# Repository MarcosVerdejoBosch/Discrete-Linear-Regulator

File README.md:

# Discrete Linear Regulator

## Download the 36 validated simulations

**[Download the assembled LTspice ZIP](https://github.com/MarcosVerdejoBosch/Discrete-Linear-Regulator/releases/download/simulations-package-v1.0.1/Discrete-Linear-Regulator-36-LTspice-v1.0.1.zip)** — 16 principal cases + 20 SIM-09 variants, with model libraries, symbols, saved plots and bias files. Extract the entire ZIP, open an ASC in `Simulaciones`, select the reference solver shown in `README.md`, and press **Run**. No CMD or Python is required. [Contents, dependencies and verification scope](publication/PORTABLE_PACKAGE.md).

**Simulation baseline closed — 2026-10-07.** The builder validated the 16 principal entries and all 20 additional SIM-09 cases. The exact local ASC/PLT files are preserved, including the final annotation layout. [Closure and recovery scope](publication/SIMULATIONS_V1.md). Open the prepared `.asc` in LTspice and press **Run**; launchers are optional. External models remain necessary. Hardware characterization and the later editorial review of the report remain separate.

A largely discrete linear regulator with selectable **5 V / 3.3 V outputs**, a fabricated PCB, and documented LTspice studies.

**Review snapshot â€” September 2026.** The assembled board has produced both output voltages. Detailed bench characterization remains pending. Numerical results below are simulations, not hardware specifications.

## Download the frozen KiCad design

**[Download the hardware-v1.0 package](https://github.com/MarcosVerdejoBosch/Discrete-Linear-Regulator/releases/download/hardware-v1.0/Discrete-Linear-Regulator-KiCad-v1.0.zip)** — final schematic, PCB, project, schematic PDF and the unchanged `Manufacturing_Regulador.zip` sent to JLCPCB. Extract and open the project in KiCad 9. [Scope and traceability](hardware/README.md).

The installed BOM still needs confirmation. [Physical measurement banks and available equipment](measurements/README.md) are documented separately; quantitative characterization remains pending.

## Run in LTspice

**2026-09-24 revalidation:** all 16 primary SIM-01–SIM-09 scenarios completed locally with LTspice 17.1.15. U17 now uses the official IRF4905 model in the full-circuit cases; report figures and tables were regenerated. The SIM-09 fixed-bias core is unchanged and was rerun. [Scope, numerical settings and evidence](publication/U17_REVALIDATION_2026-09-24.md).

Use the assembled release ZIP linked above for direct ASC execution. The older `PREPARAR_LTSPICE.cmd` and launchers are retained as optional source-development tools; they are not part of the downloadable simulation package.

The assembled package includes the supplied external dependencies. A plain **Code → Download ZIP** source snapshot is different from that package. Windows and an installed LTspice are required; see the release instructions for solver selection and third-party notices.

## Start here

- **[Read the report (PDF)](docs/regulator.pdf)** â€” architecture, implementation, simulation results and limitations.
- [Simulation index](simulation/README.md) â€” SIM-01 through SIM-09.
- [What is verified and what remains](publication/REVIEW_STATUS.md).
- [Current organized KiCad project](hardware/kicad/Regulador.kicad_pro), [schematic](hardware/kicad/Regulador.kicad_sch), [PCB](hardware/kicad/Regulador.kicad_pcb).
- [PCB routing atlas](docs/figures/pcb_subcircuit_atlas.pdf) - four component-level maps: power path, current sensing/limiting, enable control and startup. [Sources and regeneration](hardware/PCB_DOCUMENTATION.md).
- [3D board views](docs/figures/pcb_3d_views.pdf) - KiCad rendering of the final layout; standard package models and socket representations.
- [Original published KiCad snapshot](hardware/legacy-github/) â€” retained separately; it differs from the organized copy.

## Current stability finding

The nominal bench uses a 1 uF output capacitor and an **external 1 ohm series resistor**. Intrinsic capacitor ESR is additional and remains uncharacterized. The installed capacitor was identified by the builder as radial tantalum, sold as 1 uF / 35 V.

The fixed-bias regulation-core studies do **not** establish capacitor-free operation across the load range: without the external output capacitor, the near-no-load cases have negative loop margins and persistent oscillation in the corresponding transient checks. Increasing capacitance to 10 uF improves phase margin at approximately 1 A but reduces it near no load. This is not a universal recommendation for an unspecified electrolytic capacitor.

[Output-capacitor comparison and conditions](simulation/tests/SIM-09_loop_stability/results/output_cap_options/README.md).

## Repository structure

| Folder | Contents |
|---|---|
| `docs/` | Compiled report, LaTeX source, bibliography and report figures |
| `hardware/kicad/` | Organized board project |
| `hardware/legacy-github/` | Previously published board files, preserved for comparison |
| `simulation/ltspice/` | Selected scenario definitions and saved bias files |
| `simulation/tests/` | Methods, extracted metrics, selected CSVs, scripts and diagnostic comparisons |
| `publication/` | Snapshot status and provenance manifest |

## Reproduction status

The PDF is ready to read. LaTeX build instructions are in [docs/README.md](docs/README.md).

**The self-contained 36-case LTspice package is available through the release link above.** It includes the supplied models and symbols; see [package contents and verification](publication/PORTABLE_PACKAGE.md). The older [local preparation workflow](simulation/LOCAL_REVIEW.md) is retained for source-development history. Large RAW files and duplicate simulator logs remain in the local evidence archive. SHA256 records refer to those original files. Some analysis scripts require the RAW archive; preparation scripts may require additional original baseline files. Selected CSV exports support inspection without LTspice.

Scenario copies use relative model filenames. A fresh prepared folder was checked against the accepted sources, all 16 primary netlists were generated, and both SIM-09 modes were exercised through the launchers. This is local reproduction evidence, not cross-machine qualification. The [original manifest](publication/manifest.json) is historical; the [current revalidation record](publication/U17_REVALIDATION_2026-09-24.md) identifies the new results. Hardware measurements remain pending.

## License

The repository's existing [MIT license](LICENSE) is retained for project-owned material. Third-party component models and cited publications retain their own terms and are not relicensed by this repository.

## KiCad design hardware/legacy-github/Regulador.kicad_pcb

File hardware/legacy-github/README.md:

Previously published KiCad snapshot, preserved from commit 7b13f20.
The organized working copy is in ../kicad. The files differ; no equivalence is claimed.

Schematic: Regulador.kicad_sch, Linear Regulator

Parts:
C1, C2, C9, C14, C16: 100n; C_Rect_L7.2mm_W3.0mm_P5.00mm_FKS2_FKP2_MKS2_MKP2
C3: 33n; C_Rect_L7.0mm_W2.5mm_P5.00mm
C4, C5: 100p; C_Disc_D3.8mm_W2.6mm_P2.50mm
C6: 3.9n; C_Rect_L7.0mm_W2.0mm_P4.00mm
C7: 4.7n; C_Rect_L7.0mm_W2.0mm_P4.00mm
C8, C11, C13: 1u; CP_Radial_Tantal_D4.5mm_P2.50mm
C10: 6.8u; CP_Radial_Tantal_D5.0mm_P2.50mm
C12, C20, C21: 10u; CP_Radial_D5.0mm_P2.50mm
C15: 330n; C_Rect_L7.2mm_W4.5mm_P5.00mm_FKS2_FKP2_MKS2_MKP2
C17, C22: 22n; C_Rect_L7.2mm_W3.0mm_P5.00mm_FKS2_FKP2_MKS2_MKP2
C18, C19: 10n; C_Rect_L7.0mm_W2.5mm_P5.00mm
D1, D2, D3, D8, D9, D10, D13, D14, D15, D19: D_Zener; D_DO-35_SOD27_P7.62mm_Horizontal
D4, D5, D6, D7, D11, D12, D17, D18: 1N5819; D_DO-41_SOD81_P10.16mm_Horizontal
D16: LED; LED_D5.0mm
D20: TYN612; TO-220-3_Vertical
D21: 1N4148; D_DO-35_SOD27_P7.62mm_Horizontal
F1: Fuse; Fuseholder_Clip-5x20mm_Littelfuse_445-030_Inline_P20.50x5.2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
H1, H2, H3, H4: MountingHole_Pad; MountingHole_4.3mm_M4_Pad_TopOnly
INPUT1: Conn_01x02_Pin; TerminalBlock_P5.08mm
OUTPUT1: Conn_01x02_Pin; TerminalBlock_P5.08mm
Q1, Q2, Q10, Q11, Q14, Q16, Q17: BC557; TO92-Custom
Q3: BC807; SOT-23
Q4: IRF7328; SOIC-8_3.9x4.9mm_P1.27mm
Q6, Q12, Q18, Q20: IRFZ44N; TO-220-3_Vertical
Q7, Q13, Q19: 2N7000; TO92-Custom
Q8, Q21: J175; TO-92_Inline_Wide
Q15, Q23, Q24, Q25, Q26, Q27: BC547; TO92-Custom
Q_PASS1: TIP42C; TO-220-3_Vertical
Q_POL1: IRF4905; TO-220-3_Vertical
R1, R2: 200; R_Axial_DIN0207_L6.3mm_D2.5mm_P7.62mm_Horizontal
R3, R4: 270; R_Axial_DIN0207_L6.3mm_D2.5mm_P7.62mm_Horizontal
R5, R6, R9, R10, R29, R32, R48, R49, R52, R60, R61: 5.6k; R_Axial_DIN0207_L6.3mm_D2.5mm_P7.62mm_Horizontal
R12, R13, R14, R15, R16, R20, R28, R51, R54, R80, R83, R86, R89: 100; R_Axial_DIN0207_L6.3mm_D2.5mm_P7.62mm_Horizontal
R17, R21: 10; R_Axial_DIN0207_L6.3mm_D2.5mm_P7.62mm_Horizontal
R18, R19, R27, R50, R62: 20k; R_Axial_DIN0207_L6.3mm_D2.5mm_P7.62mm_Horizontal
R22, R44, R78: 7.5k; R_Axial_DIN0207_L6.3mm_D2.5mm_P7.62mm_Horizontal
R24, R63: 15k; R_Axial_DIN0207_L6.3mm_D2.5mm_P7.62mm_Horizontal
R30, R31, R70, R73, R79: 3.3k; R_Axial_DIN0207_L6.3mm_D2.5mm_P7.62mm_Horizontal
R33, R34: 1k; R_Axial_DIN0207_L6.3mm_D2.5mm_P7.62mm_Horizontal
R35, R36, R39, R40, R56, R57, R58, R65, R69, R95, R96, R103: 10k; R_Axial_DIN0207_L6.3mm_D2.5mm_P7.62mm_Horizontal
R37, R105, R107: 2k; R_Axial_DIN0207_L6.3mm_D2.5mm_P7.62mm_Horizontal
R38: 1,6k; R_Axial_DIN0207_L6.3mm_D2.5mm_P7.62mm_Horizontal
R42: 510; R_Axial_DIN0207_L6.3mm_D2.5mm_P7.62mm_Horizontal
R43, R53: 1; R_Axial_DIN0207_L6.3mm_D2.5mm_P7.62mm_Horizontal
R55, R88: 4.7k; R_Axial_DIN0207_L6.3mm_D2.5mm_P7.62mm_Horizontal
R66, R74, R77, R87, R92, R94, R97, R99, R104, R108: 100k; R_Axial_DIN0207_L6.3mm_D2.5mm_P7.62mm_Horizontal
R67, R68: 51k; R_Axial_DIN0207_L6.3mm_D2.5mm_P7.62mm_Horizontal
R71, R72: 10Meg; R_Axial_DIN0204_L3.6mm_D1.6mm_P5.08mm_Horizontal
R81: 68k; R_Axial_DIN0207_L6.3mm_D2.5mm_P7.62mm_Horizontal
R82: 680; R_Axial_DIN0207_L6.3mm_D2.5mm_P7.62mm_Horizontal
R90, R91, R93: 47k; R_Axial_DIN0207_L6.3mm_D2.5mm_P7.62mm_Horizontal
R98: 1.6k; R_Axial_DIN0207_L6.3mm_D2.5mm_P7.62mm_Horizontal
R100: 330; R_Axial_DIN0207_L6.3mm_D2.5mm_P7.62mm_Horizontal
R102, R109: 1Meg; R_Axial_DIN0207_L6.3mm_D2.5mm_P7.62mm_Horizontal
R106: 470; R_Axial_DIN0207_L6.3mm_D2.5mm_P7.62mm_Horizontal
RV1, RV2, RV3, RV4, RV5, RV6, RV7, RV8, RV9, RV10, RV11, RV12, RV13: R_Potentiometer; Potentiometer_Bourns_3296W_Vertical
Rsns1: 0.1; R_Axial_DIN0516_L15.5mm_D5.0mm_P20.32mm_Horizontal
SW1: SW_SPDT; SWITCH1; Manufacturer_Part_Number MFP113D-RA
TP4, TP5, TP6, TP7, TP8, TP9, TP10, TP11, TP16, TP17, TP18, TP19, TP20, TP21, TP22, TP23, TP26, TP27, TP28, TP29, TP30: TestPoint; TestPoint_THTPad_2.0x2.0mm_Drill1.0mm
TP24, TP25: TestPoint; TestPoint_THTPad_1.0x1.0mm_Drill0.5mm
TP_3.3V1: TestPoint; TestPoint_THTPad_2.0x2.0mm_Drill1.0mm
TP_FB1: TestPoint; TestPoint_THTPad_2.0x2.0mm_Drill1.0mm
TP_GND_IN1: TestPoint; TestPoint_THTPad_D4.0mm_Drill2.0mm
TP_GND_OUT1: TestPoint; TestPoint_THTPad_D4.0mm_Drill2.0mm
TP_Isns1: TestPoint; TestPoint_THTPad_2.0x2.0mm_Drill1.0mm
TP_OUT1: TestPoint; TestPoint_THTPad_D4.0mm_Drill2.0mm
TP_SW1: TestPoint; TestPoint_THTPad_2.0x2.0mm_Drill1.0mm
TP_TTL1: TestPoint; TestPoint_THTPad_2.0x2.0mm_Drill1.0mm
TP_VCC1: TestPoint; TestPoint_THTPad_D4.0mm_Drill2.0mm
TP_VREF1: TestPoint; TestPoint_THTPad_2.0x2.0mm_Drill1.0mm
U1, U2, U3: CA3096; DIP-16
U4: LM324A; CERDIP-14
U5, U6, U8, U11: TL431LP; TO92-Custom
U7: LM339; CERDIP-14
U9: LM393; CERDIP-8
U10: ICL7660; DIP-8_W7.62mm_Socket

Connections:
1: R79.1, R82.2, R90.1, TP23.1, U7.13
2: D21.1 (K), R89.2, R91.1, TP26.1, U4.14
/3.3V: Q7.3 (D), RV1.2, RV2.1, TP_3.3V1.1
FB: C4.2, R24.2, RV1.1, TP_FB1.1, U1.11 (B)
GND: C2.1, C8.2, C10.2, C12.2, C13.2, C15.2, C18.2, C19.2, C21.2, C22.2, D1.2 (A), D2.2 (A), D8.2 (A), D9.2 (A), D13.2 (A), D14.2 (A), D15.2 (A), D16.1 (K), D20.1 (K), H1.1, H2.1, H3.1, H4.1, INPUT1.2, OUTPUT1.2, Q3.3 (C), Q6.3 (S), Q7.1 (S), Q8.3 (S), Q12.3 (S), Q13.1 (S), Q18.3 (S), Q19.1 (S), Q20.3 (S), Q21.3 (S), Q23.3 (E), Q25.3 (E), R3.2, R4.2, R6.2, R12.2, R19.2, R27.2, R36.1, R49.2, R50.2, R56.2, R57.2, R58.2, R61.2, R68.1, R81.2, R87.1, R92.1, R94.1, R97.1, R99.1, R102.2, R103.2, R106.1, R109.2, RV2.2, RV3.2, RV5.2, RV8.2, RV11.2, RV12.2, RV13.2, SW1.MH1, SW1.MH2, TP_GND_IN1.1, TP_GND_OUT1.1, U1.16 (SUB), U2.16 (SUB), U3.2 (E), U3.16 (SUB), U4.11 (V-), U5.2 (A), U6.2 (A), U7.12 (V-), U8.2 (A), U9.4 (V-), U10.3 (GND), U10.5 (VOUT), U11.2 (A)
LDO2: R70.1, R71.1, R93.1, TP16.1, U7.1, U9.6 (-)
unnamed: C1.2, R5.2, R6.1
unnamed: C2.2, R9.2, R10.1
unnamed: C5.2, R35.2, R39.1, TP_Isns1.1, U4.1
unnamed: C6.1, R37.1
unnamed: C7.1, R42.2, U4.7
unnamed: C7.2, R38.1
unnamed: C8.1, R43.2
unnamed: C9.2, R48.2, R49.1
unnamed: C14.2, R60.2, R61.1
unnamed: C15.1, R63.1, R65.2, R69.2, U7.2
unnamed: D1.1 (K), Q6.1 (G), R19.1, R20.1, TP_TTL1.1
unnamed: D2.1 (K), Q7.2 (G), R27.1, R28.1, TP_SW1.1
unnamed: D3.2 (A), Q_POL1.1 (G), R103.1
unnamed: D4.2 (A), F1.2, U10.8 (V+)
unnamed: C6.2, D5.2 (A), U1.6 (C), U1.8 (B), U1.12 (C)
unnamed: D5.1 (K), R42.1
unnamed: D6.1 (K), D7.2 (A), Q10.2 (B), Q11.1 (C), R48.1
unnamed: D7.1 (K), Q10.3 (E), Q11.2 (B), RV6.2
unnamed: D9.1 (K), Q12.1 (G), R51.1, R52.2
unnamed: D10.2 (A), Q4.4, Q14.1 (C), R56.1
unnamed: D11.2 (A), D12.1 (K), Q16.2 (B), Q17.1 (C), R60.1
unnamed: D11.1 (K), Q16.3 (E), Q17.2 (B), RV7.2
unnamed: D13.1 (K), Q18.1 (G), R78.2, R80.1
unnamed: C16.2, D14.1 (K), Q19.2 (G), R81.1, R82.1
unnamed: C17.2, D15.1 (K), Q20.1 (G), R88.2, R89.1
unnamed: D16.2 (A), R100.1
unnamed: C20.1, D4.1 (K), D17.2 (A)
unnamed: C3.1, D18.2 (A), Q_PASS1.2 (C), R33.1, Rsns1.1
unnamed: C22.1, D19.2 (A), D20.3 (G), R106.2
unnamed: D8.1 (K), D21.2 (A), Q13.2 (G), R50.1, R54.1
unnamed: Q1.2 (B), Q2.1 (C), R5.1
unnamed: Q1.1 (C), R1.1, R2.1, TP30.1
unnamed: Q1.3 (E), Q2.2 (B), RV4.2, TP29.1
unnamed: Q3.1 (B), R37.2, U2.6 (C), U2.15 (C)
unnamed: Q3.2 (E), Q4.7, U3.12 (C), U3.15 (C)
unnamed: Q4.1, R18.1, R21.2
unnamed: Q4.2, R17.1, R18.2
unnamed: Q6.2 (D), R17.2
unnamed: Q8.2 (G), R102.1, R104.2, TP10.1
unnamed: Q12.2 (D), R53.2
unnamed: Q13.3 (D), R51.2
unnamed: Q14.2 (B), Q15.1 (C), R55.2
unnamed: C11.2, Q15.2 (B), R58.1
unnamed: Q15.3 (E), R57.1
unnamed: Q18.2 (D), R83.2
unnamed: C16.1, Q19.3 (D), R80.2
unnamed: C17.1, Q20.2 (D), R86.2
unnamed: Q21.2 (G), R108.2, R109.1, TP27.1
unnamed: Q23.2 (B), R96.1, R97.2
unnamed: Q24.3 (E), R100.2
unnamed: Q25.2 (B), R87.2, R90.2
unnamed: Q25.1 (C), Q26.3 (E)
unnamed: C18.1, Q26.2 (B), R91.2, R92.2
unnamed: Q26.1 (C), Q27.3 (E)
unnamed: C19.1, Q27.2 (B), R93.2, R94.2
unnamed: Q27.1 (C), R95.1, R96.2
unnamed: C3.2, Q_PASS1.1 (B), R21.1, R22.2
unnamed: R83.1, RV10.2, RV11.1, TP22.1
unnamed: R86.1, RV8.1, RV9.2, TP25.1
unnamed: R29.2, R104.1, U9.1
unnamed: R32.2, R108.1, U9.7
unnamed: R28.2, SW1.3 (NO)
unnamed: U1.1 (B), U1.3 (C), U1.5 (B), U1.15 (C)
unnamed: U1.2 (E), U2.3 (C)
unnamed: U1.4 (E), U2.1 (B), U2.8 (B), U2.9 (C)
unnamed: U1.7 (E), U2.5 (B), U3.6 (C)
unnamed: R2.2, U1.10 (E)
unnamed: R44.2, U1.14 (B)
unnamed: R1.2, U1.13 (E)
unnamed: R3.1, U2.2 (E)
unnamed: R12.1, U2.4 (E)
unnamed: R4.1, U2.7 (E)
unnamed: U2.11 (B), U2.12 (C), U2.14 (B), U3.9 (C), U3.11 (B), U3.14 (B)
unnamed: R13.2, TP4.1, U2.10 (E)
unnamed: R14.2, TP5.1, U2.13 (E)
unnamed: RV3.1, U3.1 (B), U3.4 (E)
unnamed: R9.1, U3.3 (C), U3.5 (B), U3.8 (B)
unnamed: RV5.1, TP8.1, U3.7 (E)
unnamed: R15.2, TP6.1, U3.10 (E)
unnamed: R16.2, TP7.1, U3.13 (E)
unnamed: R33.2, R36.2, U4.3 (+)
unnamed: C5.1, R34.2, R35.1, U4.2 (-)
unnamed: U4.5 (+), U4.8, U4.9 (-)
unnamed: R38.2, R39.2, U4.6 (-)
unnamed: R40.1, RV13.1, TP9.1, U4.10 (+)
unnamed: R77.1, RV9.1, TP24.1, U4.13 (-)
unnamed: R62.2, RV12.1, TP20.1, U7.5 (+)
unnamed: R65.1, R71.2, U7.7 (+)
unnamed: R66.1, R67.1, TP18.1, U7.6 (-)
unnamed: R74.1, RV10.1, TP21.1, U7.11 (+)
unnamed: R69.1, R72.2, U7.9 (+)
unnamed: R67.2, R68.2, TP19.1, U7.8 (-)
unnamed: R30.2, TP11.1, U8.3 (K), U9.2 (-)
unnamed: R105.2, U8.1 (REF)
unnamed: C20.2, U10.2 (CAP+)
unnamed: R31.2, TP28.1, U9.5 (+), U11.3 (K)
unnamed: R107.2, U11.1 (REF)
OUT: C4.1, OUTPUT1.1, Q8.1 (D), R24.1, R34.1, R43.1, R105.1, Rsns1.2, TP_OUT1.1
REF2: C13.1, D12.2 (A), Q16.1 (C), U4.12 (+), U6.1 (REF), U6.3 (K), U7.4 (-), U7.10 (-)
TL1: R54.2, R72.1, R73.2, TP17.1, U7.14
TTL: Q23.1 (C), Q24.2 (B), R20.2, R98.1, R99.2, U9.3 (+)
VCC: INPUT1.1, Q_POL1.2 (D), TP_VCC1.1
VCTRL: C9.1, C11.1, C12.1, D18.1 (K), Q4.5, Q11.3 (E), Q21.1 (D), Q_PASS1.3 (E), R22.1, R62.1, R107.1, RV6.1
VDOBL: C21.1, D17.1 (K), D19.1 (K), D20.2 (A), R29.1, R30.1, R31.1, R32.1, U9.8 (V+)
VEE: C1.1, C14.1, D3.1 (K), D10.1 (K), F1.1, Q2.3 (E), Q4.3, Q14.3 (E), Q17.3 (E), Q24.1 (C), Q_POL1.3 (S), R10.2, R13.1, R14.1, R15.1, R16.1, R52.1, R55.1, R63.2, R66.2, R70.2, R73.1, R74.2, R77.2, R78.1, R79.2, R88.1, R95.2, R98.2, RV4.1, RV7.1, SW1.2 (COM), U1.9 (C), U4.4 (V+), U7.3 (V+)
VREF: C10.1, D6.2 (A), Q10.1 (C), R40.2, R44.1, R53.1, TP_VREF1.1, U5.1 (REF), U5.3 (K)

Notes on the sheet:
Time Delay
270
75k
18k
X7R o C0G
560
VZENER 15V
Regulator Enable
Peripherals
Poliéster
Start Up
13k
Cerámico NP0 / C0G
1.2k
VREF
25k
GROUND SHUNT
VREF AUX
27k
500 mA
29k
X7R, C0G o Poliéster
6.8k
UVLO
Doubler
OVLO
Regulator

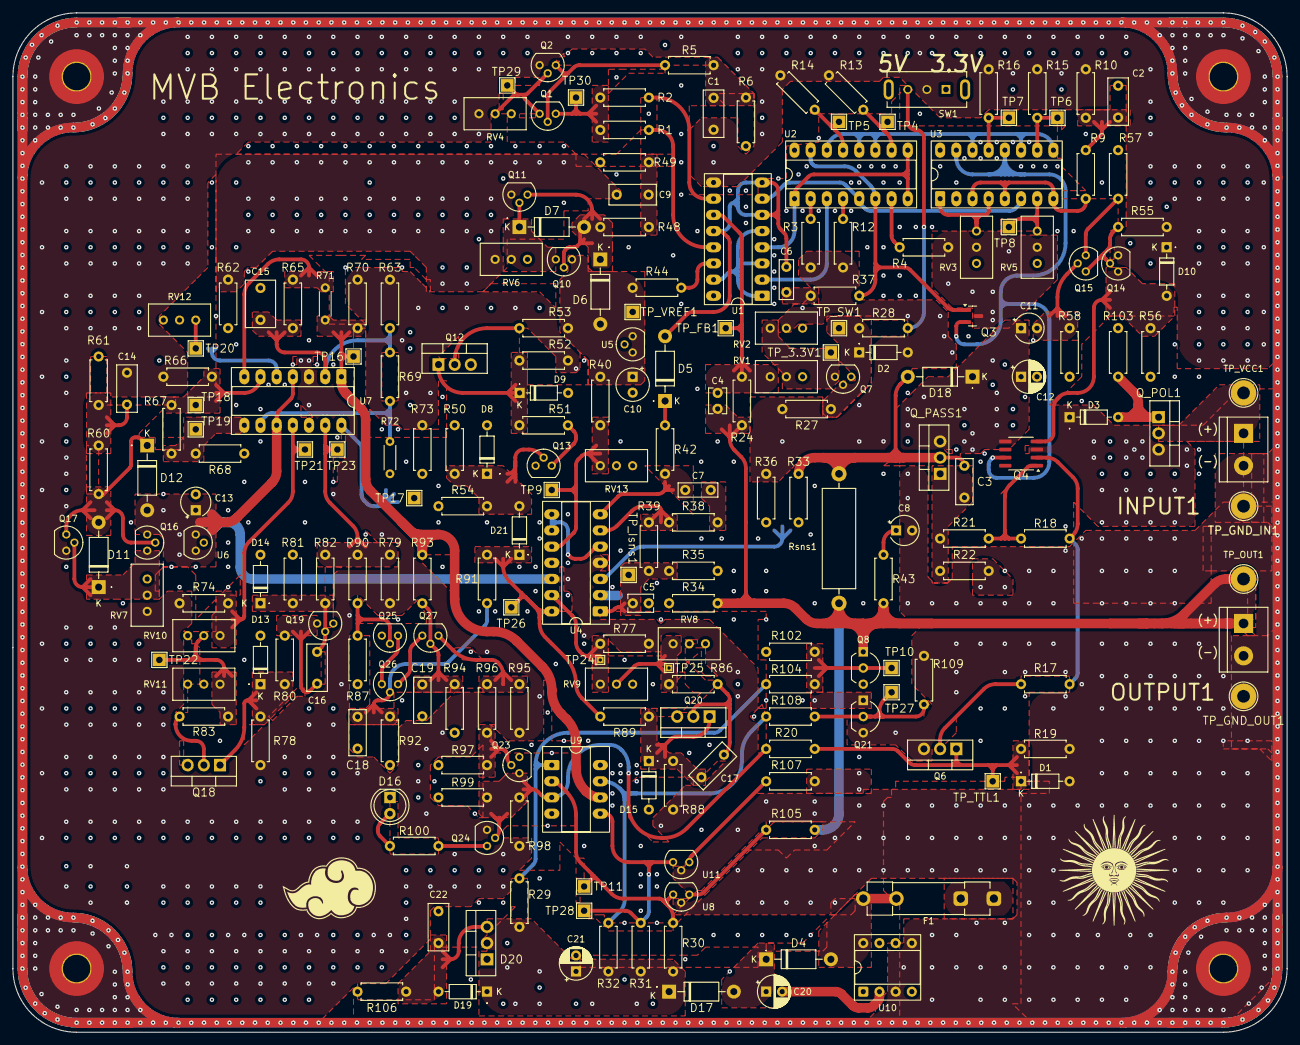
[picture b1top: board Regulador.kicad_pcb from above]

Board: 4 copper layers, 200.0 x 160.0 mm, 227 parts (0 on the bottom side), 112 nets.

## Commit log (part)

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2025-11-07 Create Kicad
    Add KiCad project files
2025-11-07 Update and rename Regulador.kicad_sch to KiCad/Regulador.kicad_sch
    Move KiCad project files
